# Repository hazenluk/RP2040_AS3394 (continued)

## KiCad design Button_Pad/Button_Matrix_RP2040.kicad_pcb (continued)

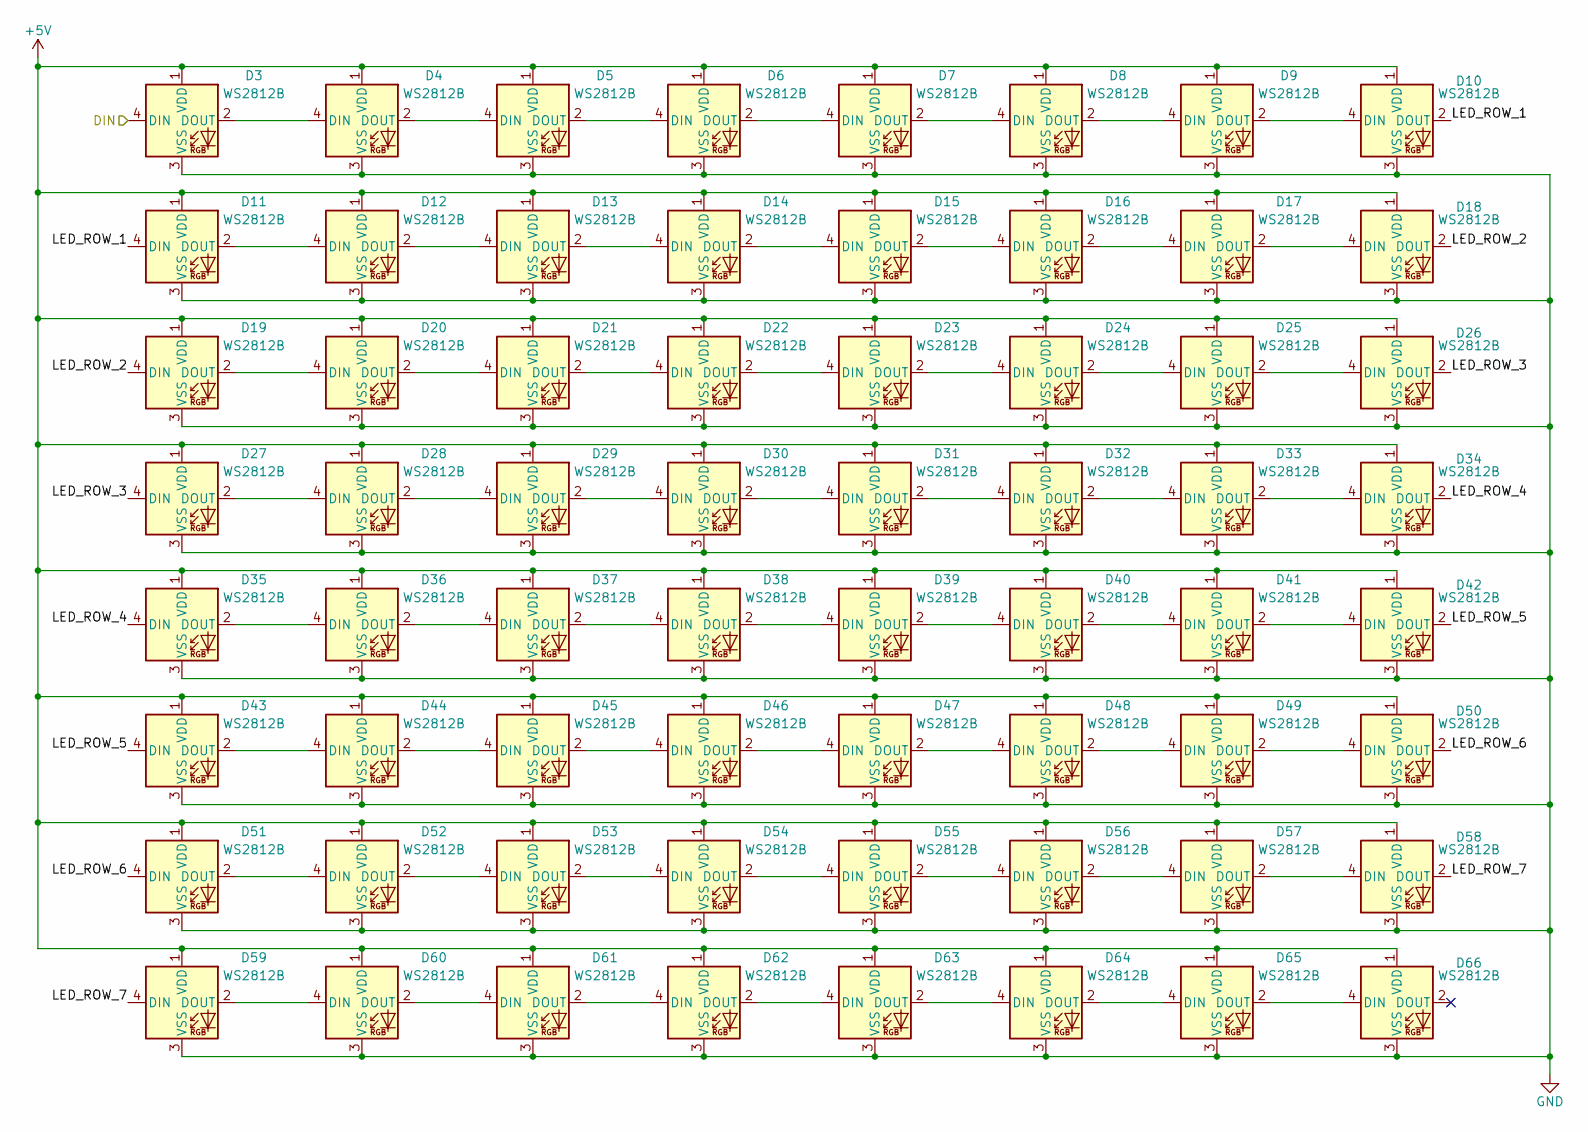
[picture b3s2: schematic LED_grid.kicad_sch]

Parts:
D3, D4, D5, D6, D7, D8, D9, D10, D11, D12, D13, D14, D15, D16, D17, D18, D19, D20, D21, D22, D23, D24, D25, D26, D27, D28, D29, D30, D31, D32, D33, D34, D35, D36, D37, D38, D39, D40, D41, D42, D43, D44, D45, D46, D47, D48, D49, D50, D51, D52, D53, D54, D55, D56, D57, D58, D59, D60, D61, D62, D63, D64, D65, D66: WS2812B; LED_WS2812B-2020_PLCC4_2.0x2.0mm

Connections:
/LED_grid/DIN: D3.4 (DIN); also elsewhere on the board
/LED_grid/LED_ROW_1: D10.2 (DOUT), D11.4 (DIN)
/LED_grid/LED_ROW_2: D18.2 (DOUT), D19.4 (DIN)
/LED_grid/LED_ROW_3: D26.2 (DOUT), D27.4 (DIN)
/LED_grid/LED_ROW_4: D34.2 (DOUT), D35.4 (DIN)
/LED_grid/LED_ROW_5: D42.2 (DOUT), D43.4 (DIN)
/LED_grid/LED_ROW_6: D50.2 (DOUT), D51.4 (DIN)
/LED_grid/LED_ROW_7: D58.2 (DOUT), D59.4 (DIN)
GND: D3.3 (VSS), D4.3 (VSS), D5.3 (VSS), D6.3 (VSS), D7.3 (VSS), D8.3 (VSS), D9.3 (VSS), D10.3 (VSS), D11.3 (VSS), D12.3 (VSS), D13.3 (VSS), D14.3 (VSS), D15.3 (VSS), D16.3 (VSS), D17.3 (VSS), D18.3 (VSS), D19.3 (VSS), D20.3 (VSS), D21.3 (VSS), D22.3 (VSS), D23.3 (VSS), D24.3 (VSS), D25.3 (VSS), D26.3 (VSS), D27.3 (VSS), D28.3 (VSS), D29.3 (VSS), D30.3 (VSS), D31.3 (VSS), D32.3 (VSS), D33.3 (VSS), D34.3 (VSS), D35.3 (VSS), D36.3 (VSS), D37.3 (VSS), D38.3 (VSS), D39.3 (VSS), D40.3 (VSS), D41.3 (VSS), D42.3 (VSS), D43.3 (VSS), D44.3 (VSS), D45.3 (VSS), D46.3 (VSS), D47.3 (VSS), D48.3 (VSS), D49.3 (VSS), D50.3 (VSS), D51.3 (VSS), D52.3 (VSS), D53.3 (VSS), D54.3 (VSS), D55.3 (VSS), D56.3 (VSS), D57.3 (VSS), D58.3 (VSS), D59.3 (VSS), D60.3 (VSS), D61.3 (VSS), D62.3 (VSS), D63.3 (VSS), D64.3 (VSS), D65.3 (VSS), D66.3 (VSS); also elsewhere on the board
unnamed: D3.2 (DOUT), D4.4 (DIN)
unnamed: D4.2 (DOUT), D5.4 (DIN)
unnamed: D5.2 (DOUT), D6.4 (DIN)
unnamed: D6.2 (DOUT), D7.4 (DIN)
unnamed: D7.2 (DOUT), D8.4 (DIN)
unnamed: D8.2 (DOUT), D9.4 (DIN)
unnamed: D9.2 (DOUT), D10.4 (DIN)
unnamed: D11.2 (DOUT), D12.4 (DIN)
unnamed: D12.2 (DOUT), D13.4 (DIN)
unnamed: D13.2 (DOUT), D14.4 (DIN)
unnamed: D14.2 (DOUT), D15.4 (DIN)
unnamed: D15.2 (DOUT), D16.4 (DIN)
unnamed: D16.2 (DOUT), D17.4 (DIN)
unnamed: D17.2 (DOUT), D18.4 (DIN)
unnamed: D19.2 (DOUT), D20.4 (DIN)
unnamed: D20.2 (DOUT), D21.4 (DIN)
unnamed: D21.2 (DOUT), D22.4 (DIN)
unnamed: D22.2 (DOUT), D23.4 (DIN)
unnamed: D23.2 (DOUT), D24.4 (DIN)
unnamed: D24.2 (DOUT), D25.4 (DIN)
unnamed: D25.2 (DOUT), D26.4 (DIN)
unnamed: D27.2 (DOUT), D28.4 (DIN)
unnamed: D28.2 (DOUT), D29.4 (DIN)
unnamed: D29.2 (DOUT), D30.4 (DIN)
unnamed: D30.2 (DOUT), D31.4 (DIN)
unnamed: D31.2 (DOUT), D32.4 (DIN)
unnamed: D32.2 (DOUT), D33.4 (DIN)
unnamed: D33.2 (DOUT), D34.4 (DIN)
unnamed: D35.2 (DOUT), D36.4 (DIN)
unnamed: D36.2 (DOUT), D37.4 (DIN)
unnamed: D37.2 (DOUT), D38.4 (DIN)
unnamed: D38.2 (DOUT), D39.4 (DIN)
unnamed: D39.2 (DOUT), D40.4 (DIN)
unnamed: D40.2 (DOUT), D41.4 (DIN)
unnamed: D41.2 (DOUT), D42.4 (DIN)
unnamed: D43.2 (DOUT), D44.4 (DIN)
unnamed: D44.2 (DOUT), D45.4 (DIN)
unnamed: D45.2 (DOUT), D46.4 (DIN)
unnamed: D46.2 (DOUT), D47.4 (DIN)
unnamed: D47.2 (DOUT), D48.4 (DIN)
unnamed: D48.2 (DOUT), D49.4 (DIN)
unnamed: D49.2 (DOUT), D50.4 (DIN)
unnamed: D51.2 (DOUT), D52.4 (DIN)
unnamed: D52.2 (DOUT), D53.4 (DIN)
unnamed: D53.2 (DOUT), D54.4 (DIN)
unnamed: D54.2 (DOUT), D55.4 (DIN)
unnamed: D55.2 (DOUT), D56.4 (DIN)
unnamed: D56.2 (DOUT), D57.4 (DIN)
unnamed: D57.2 (DOUT), D58.4 (DIN)
unnamed: D59.2 (DOUT), D60.4 (DIN)
unnamed: D60.2 (DOUT), D61.4 (DIN)
unnamed: D61.2 (DOUT), D62.4 (DIN)
unnamed: D62.2 (DOUT), D63.4 (DIN)
unnamed: D63.2 (DOUT), D64.4 (DIN)
unnamed: D64.2 (DOUT), D65.4 (DIN)
unnamed: D65.2 (DOUT), D66.4 (DIN)

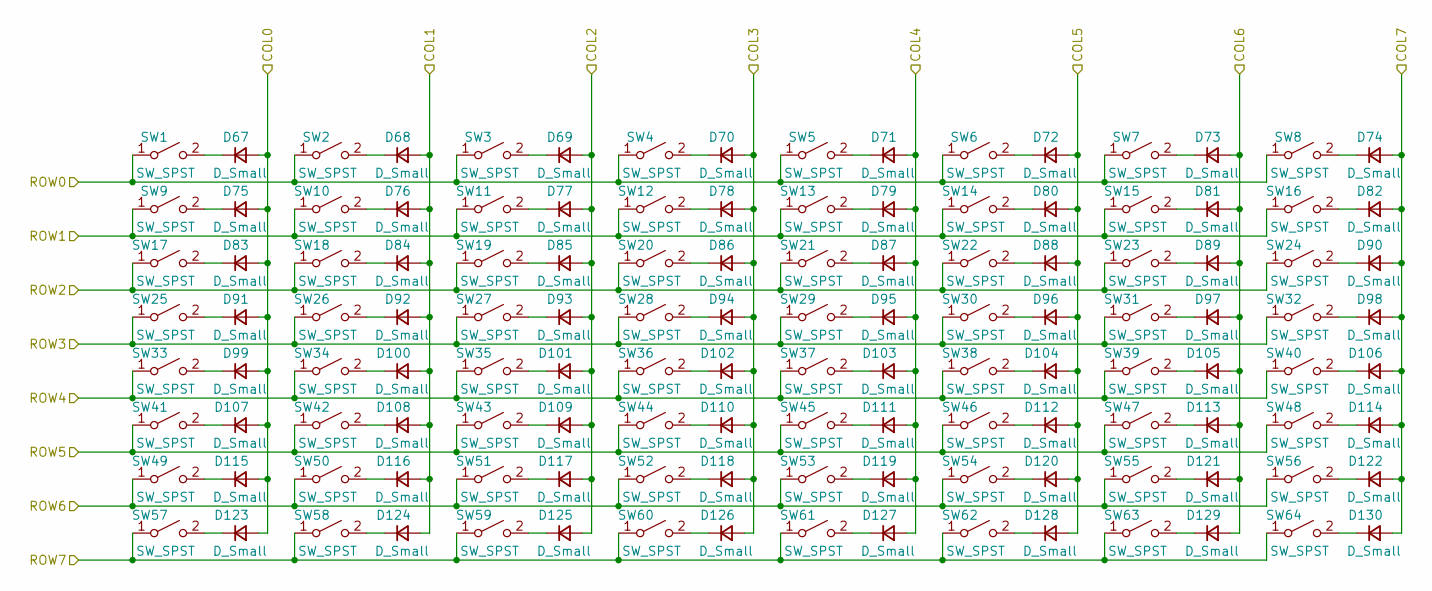
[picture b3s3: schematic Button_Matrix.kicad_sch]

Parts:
D67, D68, D69, D70, D71, D72, D73, D74, D75, D76, D77, D78, D79, D80, D81, D82, D83, D84, D85, D86, D87, D88, D89, D90, D91, D92, D93, D94, D95, D96, D97, D98, D99, D100, D101, D102, D103, D104, D105, D106, D107, D108, D109, D110, D111, D112, D113, D114, D115, D116, D117, D118, D119, D120, D121, D122, D123, D124, D125, D126, D127, D128, D129, D130: D_Small; D_SOD-323
SW1, SW2, SW3, SW4, SW5, SW6, SW7, SW8, SW9, SW10, SW11, SW12, SW13, SW14, SW15, SW16, SW17, SW18, SW19, SW20, SW21, SW22, SW23, SW24, SW25, SW26, SW27, SW28, SW29, SW30, SW31, SW32, SW33, SW34, SW35, SW36, SW37, SW38, SW39, SW40, SW41, SW42, SW43, SW44, SW45, SW46, SW47, SW48, SW49, SW50, SW51, SW52, SW53, SW54, SW55, SW56, SW57, SW58, SW59, SW60, SW61, SW62, SW63, SW64: SW_SPST; MICROBUILDER_ELAST_PAD_SQUARE_10MM_4X4WIDE

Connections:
/Button_Matrix/COL0: D67.2 (A), D75.2 (A), D83.2 (A), D91.2 (A), D99.2 (A), D107.2 (A), D115.2 (A), D123.2 (A); also elsewhere on the board
/Button_Matrix/COL1: D68.2 (A), D76.2 (A), D84.2 (A), D92.2 (A), D100.2 (A), D108.2 (A), D116.2 (A), D124.2 (A); also elsewhere on the board
/Button_Matrix/COL2: D69.2 (A), D77.2 (A), D85.2 (A), D93.2 (A), D101.2 (A), D109.2 (A), D117.2 (A), D125.2 (A); also elsewhere on the board
/Button_Matrix/COL3: D70.2 (A), D78.2 (A), D86.2 (A), D94.2 (A), D102.2 (A), D110.2 (A), D118.2 (A), D126.2 (A); also elsewhere on the board
/Button_Matrix/COL4: D71.2 (A), D79.2 (A), D87.2 (A), D95.2 (A), D103.2 (A), D111.2 (A), D119.2 (A), D127.2 (A); also elsewhere on the board
/Button_Matrix/COL5: D72.2 (A), D80.2 (A), D88.2 (A), D96.2 (A), D104.2 (A), D112.2 (A), D120.2 (A), D128.2 (A); also elsewhere on the board
/Button_Matrix/COL6: D73.2 (A), D81.2 (A), D89.2 (A), D97.2 (A), D105.2 (A), D113.2 (A), D121.2 (A), D129.2 (A); also elsewhere on the board
/Button_Matrix/COL7: D74.2 (A), D82.2 (A), D90.2 (A), D98.2 (A), D106.2 (A), D114.2 (A), D122.2 (A), D130.2 (A); also elsewhere on the board
/Button_Matrix/ROW0: SW1.1 (A), SW2.1 (A), SW3.1 (A), SW4.1 (A), SW5.1 (A), SW6.1 (A), SW7.1 (A), SW8.1 (A); also elsewhere on the board
/Button_Matrix/ROW1: SW9.1 (A), SW10.1 (A), SW11.1 (A), SW12.1 (A), SW13.1 (A), SW14.1 (A), SW15.1 (A), SW16.1 (A); also elsewhere on the board
/Button_Matrix/ROW2: SW17.1 (A), SW18.1 (A), SW19.1 (A), SW20.1 (A), SW21.1 (A), SW22.1 (A), SW23.1 (A), SW24.1 (A); also elsewhere on the board
/Button_Matrix/ROW3: SW25.1 (A), SW26.1 (A), SW27.1 (A), SW28.1 (A), SW29.1 (A), SW30.1 (A), SW31.1 (A), SW32.1 (A); also elsewhere on the board
/Button_Matrix/ROW4: SW33.1 (A), SW34.1 (A), SW35.1 (A), SW36.1 (A), SW37.1 (A), SW38.1 (A), SW39.1 (A), SW40.1 (A); also elsewhere on the board
/Button_Matrix/ROW5: SW41.1 (A), SW42.1 (A), SW43.1 (A), SW44.1 (A), SW45.1 (A), SW46.1 (A), SW47.1 (A), SW48.1 (A); also elsewhere on the board
/Button_Matrix/ROW6: SW49.1 (A), SW50.1 (A), SW51.1 (A), SW52.1 (A), SW53.1 (A), SW54.1 (A), SW55.1 (A), SW56.1 (A); also elsewhere on the board
/Button_Matrix/ROW7: SW57.1 (A), SW58.1 (A), SW59.1 (A), SW60.1 (A), SW61.1 (A), SW62.1 (A), SW63.1 (A), SW64.1 (A); also elsewhere on the board
unnamed: D67.1 (K), SW1.2 (B)
unnamed: D68.1 (K), SW2.2 (B)
unnamed: D69.1 (K), SW3.2 (B)
unnamed: D70.1 (K), SW4.2 (B)
unnamed: D71.1 (K), SW5.2 (B)
unnamed: D72.1 (K), SW6.2 (B)
unnamed: D73.1 (K), SW7.2 (B)
unnamed: D74.1 (K), SW8.2 (B)
unnamed: D75.1 (K), SW9.2 (B)
unnamed: D76.1 (K), SW10.2 (B)
unnamed: D77.1 (K), SW11.2 (B)
unnamed: D78.1 (K), SW12.2 (B)
unnamed: D79.1 (K), SW13.2 (B)
unnamed: D80.1 (K), SW14.2 (B)
unnamed: D81.1 (K), SW15.2 (B)
unnamed: D82.1 (K), SW16.2 (B)
unnamed: D83.1 (K), SW17.2 (B)
unnamed: D84.1 (K), SW18.2 (B)
unnamed: D85.1 (K), SW19.2 (B)
unnamed: D86.1 (K), SW20.2 (B)
unnamed: D87.1 (K), SW21.2 (B)
unnamed: D88.1 (K), SW22.2 (B)
unnamed: D89.1 (K), SW23.2 (B)
unnamed: D90.1 (K), SW24.2 (B)
unnamed: D91.1 (K), SW25.2 (B)
unnamed: D92.1 (K), SW26.2 (B)
unnamed: D93.1 (K), SW27.2 (B)
unnamed: D94.1 (K), SW28.2 (B)
unnamed: D95.1 (K), SW29.2 (B)
unnamed: D96.1 (K), SW30.2 (B)
unnamed: D97.1 (K), SW31.2 (B)
unnamed: D98.1 (K), SW32.2 (B)
unnamed: D99.1 (K), SW33.2 (B)
unnamed: D100.1 (K), SW34.2 (B)
unnamed: D101.1 (K), SW35.2 (B)
unnamed: D102.1 (K), SW36.2 (B)
unnamed: D103.1 (K), SW37.2 (B)
unnamed: D104.1 (K), SW38.2 (B)
unnamed: D105.1 (K), SW39.2 (B)
unnamed: D106.1 (K), SW40.2 (B)
unnamed: D107.1 (K), SW41.2 (B)
unnamed: D108.1 (K), SW42.2 (B)
unnamed: D109.1 (K), SW43.2 (B)
unnamed: D110.1 (K), SW44.2 (B)
unnamed: D111.1 (K), SW45.2 (B)
unnamed: D112.1 (K), SW46.2 (B)
unnamed: D113.1 (K), SW47.2 (B)
unnamed: D114.1 (K), SW48.2 (B)
unnamed: D115.1 (K), SW49.2 (B)
unnamed: D116.1 (K), SW50.2 (B)
unnamed: D117.1 (K), SW51.2 (B)
unnamed: D118.1 (K), SW52.2 (B)
unnamed: D119.1 (K), SW53.2 (B)
unnamed: D120.1 (K), SW54.2 (B)
unnamed: D121.1 (K), SW55.2 (B)
unnamed: D122.1 (K), SW56.2 (B)
unnamed: D123.1 (K), SW57.2 (B)
unnamed: D124.1 (K), SW58.2 (B)
unnamed: D125.1 (K), SW59.2 (B)
unnamed: D126.1 (K), SW60.2 (B)
unnamed: D127.1 (K), SW61.2 (B)
unnamed: D128.1 (K), SW62.2 (B)
unnamed: D129.1 (K), SW63.2 (B)
unnamed: D130.1 (K), SW64.2 (B)

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
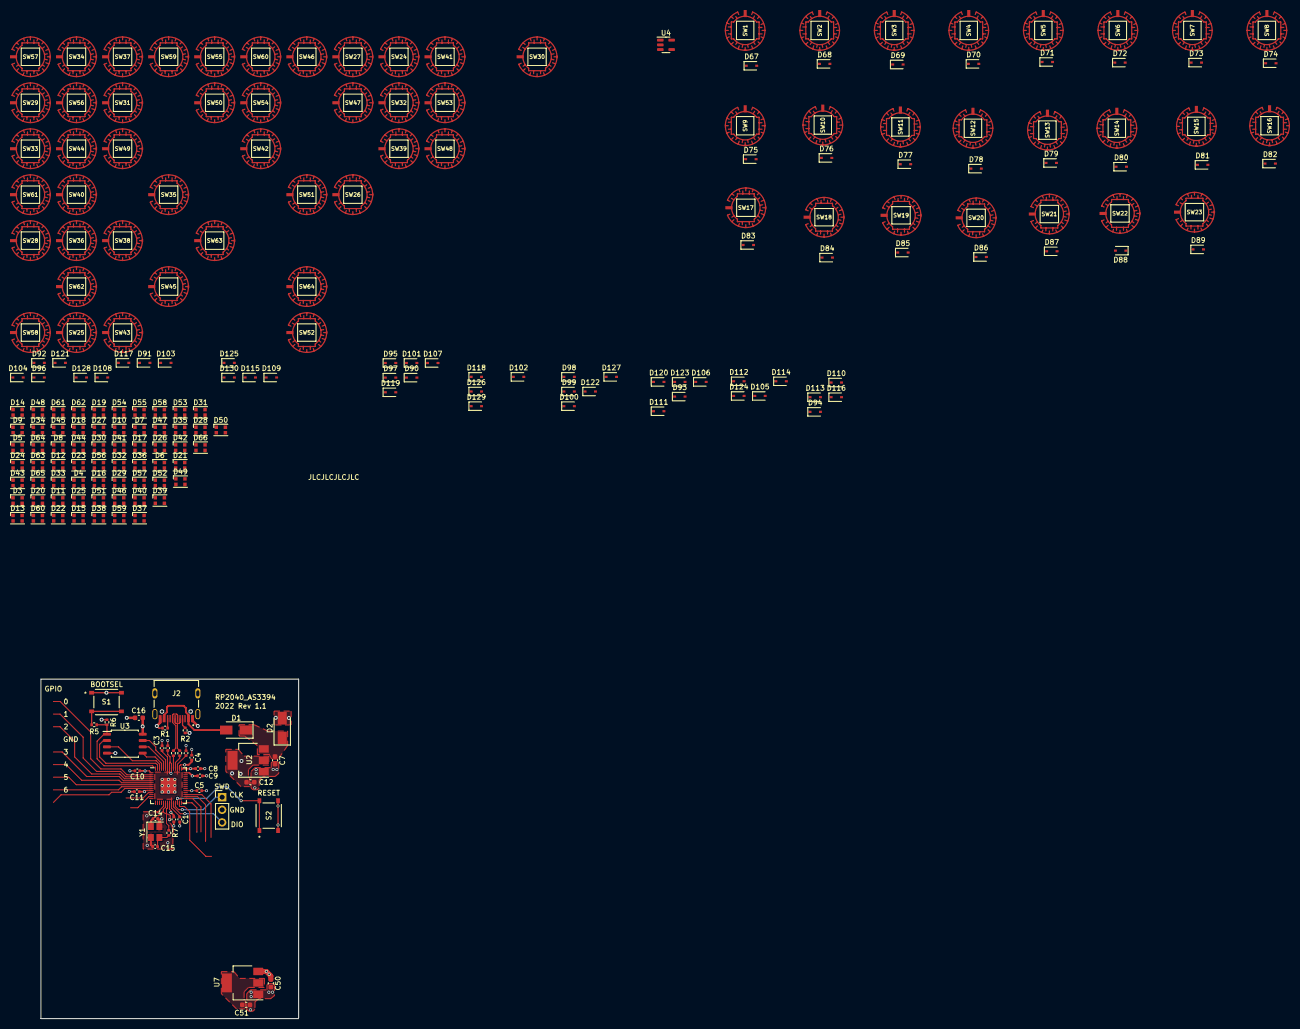
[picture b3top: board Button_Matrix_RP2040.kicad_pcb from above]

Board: 4 copper layers, 51.8 x 68.3 mm, 229 parts (0 on the bottom side), 170 nets.

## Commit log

2022-09-13 Upload to GitHub. Schematic nearly complete; need to add stereo VCA.
2022-09-13 Added README.md
2022-09-14 Finished schema; decided to make voice cards mono and leave stereo mixing to mainboards instead
2022-09-14 Last commit was a lie. Added bypass caps and power conns to LM324s.
2022-10-10 Added PWM connections from RP2040 to subsheet containing AS3394; finished assinging components for JLC assembly
2022-10-15 Started placement
2022-10-25 Finished most of routing; added TL071 for headphone out; working on adding I/O
2022-10-25 Mostly finished, just need to review and add final touches
2022-10-25 Added WIP photo of board
2022-10-25 Added WIP photo to README
2022-10-28 Moved silkscreen designators so they're mostly readable. Rerouted some traces on bottom layer so they don't cross power planes with different potentials
2022-11-05 First board prototype ordered from JLC with assembly
2022-11-11 Fixed diff pair polarity
2022-12-20 continuing work on second version
2022-12-20 Added code (WIP)
2023-02-07 added separate LDO for 3394, removed amp, designed psu board and made project for carrier board
2023-03-17 Updated to Kicad 7
2023-03-18 Reworked op-amp bias to use 5V LDO reference instead of 6.5V vin
2023-09-14 Still WIP. Project mostly abandoned in favor of multiplexed DAC approach.
